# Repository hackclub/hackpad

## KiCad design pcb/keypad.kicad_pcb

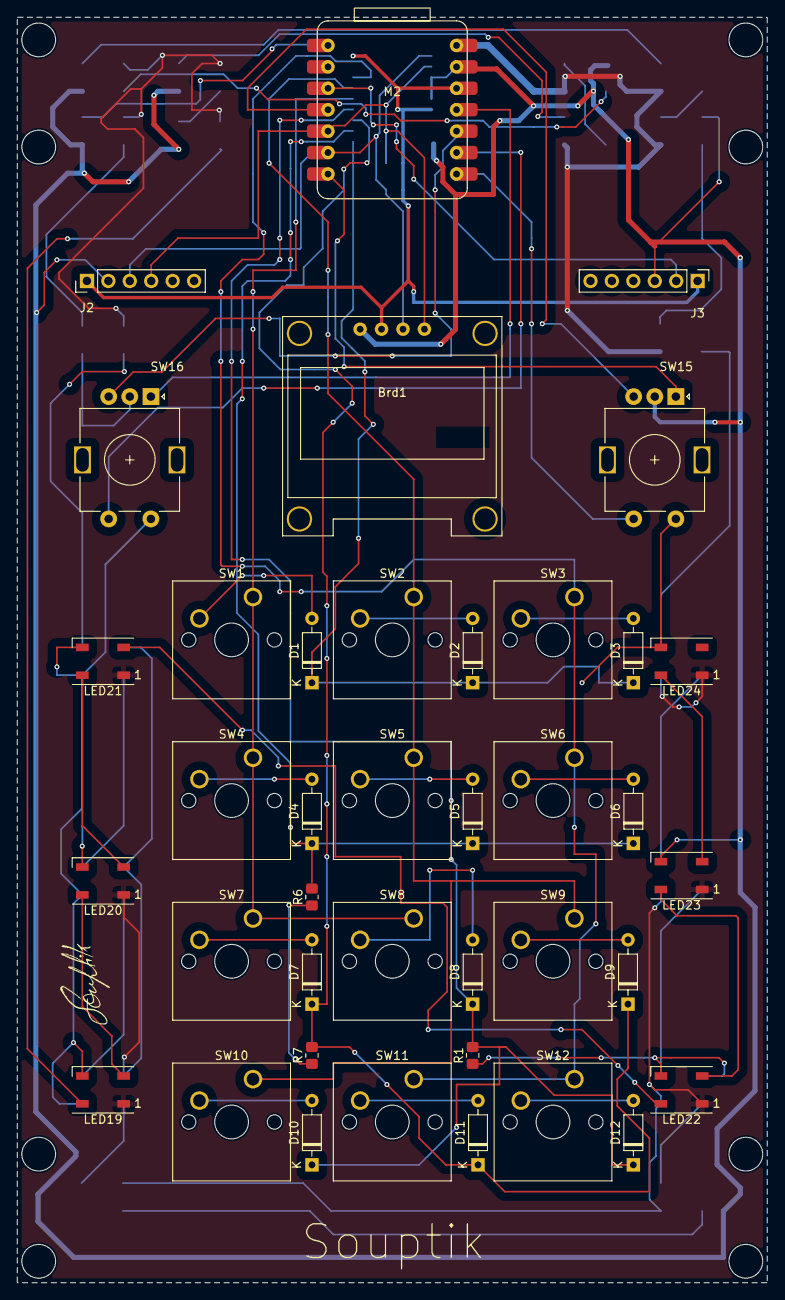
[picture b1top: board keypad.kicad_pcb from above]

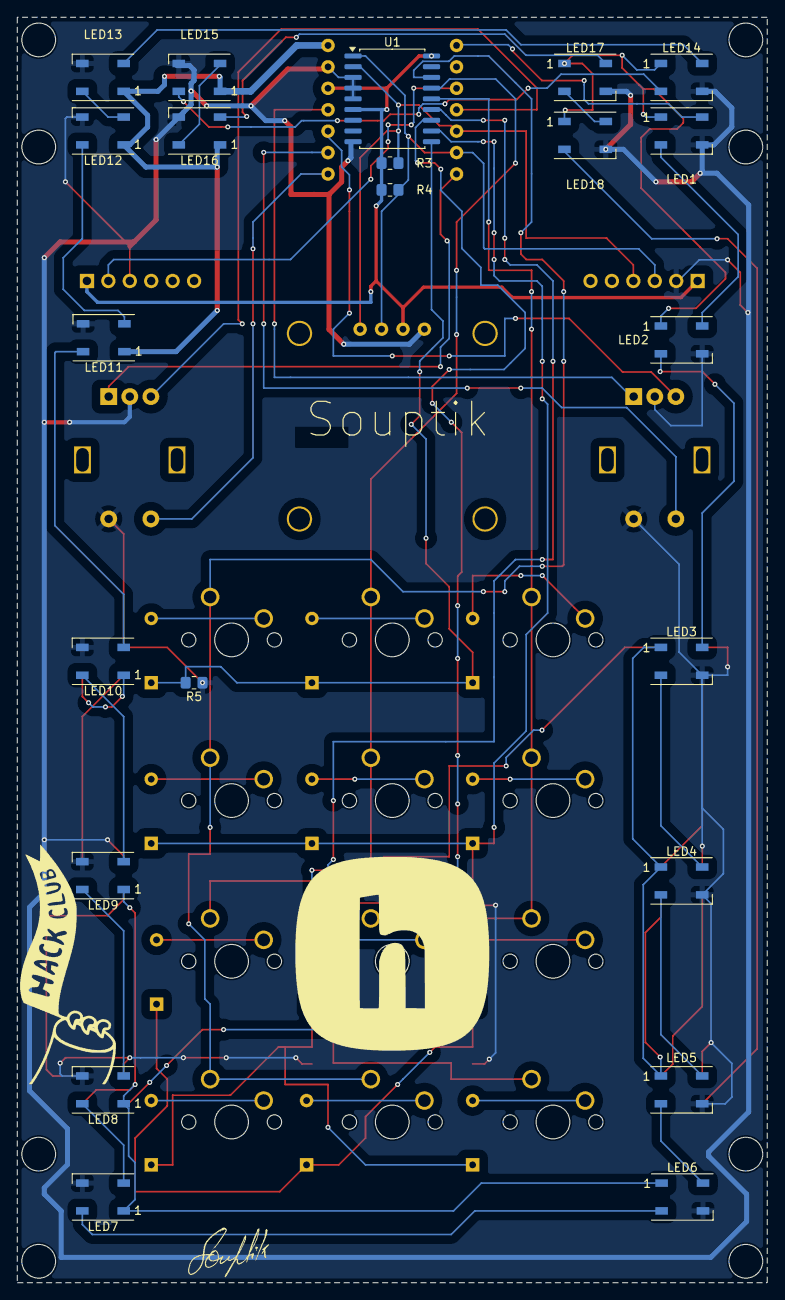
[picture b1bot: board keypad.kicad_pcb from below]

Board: 2 copper layers, 88.9 x 150.0 mm, 61 parts (22 on the bottom side), 55 nets.

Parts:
Brd1: SSD1306; SSD1306_0.96_Oled
D1, D2, D3, D4, D5, D6, D7, D8, D9, D10, D11, D12: D; D_DO-35_SOD27_P7.62mm_Horizontal
J2: VL53L0X; PinHeader_1x06_P2.54mm_Vertical
J3: DHT11; PinHeader_1x06_P2.54mm_Vertical
LED1, LED2, LED3, LED4, LED5, LED6, LED7, LED8, LED9, LED10, LED11, LED12, LED13, LED14, LED15, LED16, LED17, LED18, LED19, LED20, LED21, LED22, LED23, LED24: WS2812B; LED_WS2812B_PLCC4_5.0x5.0mm_P3.2mm
M2: MOUDLE-SEEEDUINO-XIAO; RP2040
R1, R5, R6, R7: 10K; R_0805_2012Metric_Pad1.20x1.40mm_HandSolder
R3, R4: 4.7K; R_0805_2012Metric_Pad1.20x1.40mm_HandSolder
SW1, SW2, SW3, SW4, SW5, SW6, SW7, SW8, SW9, SW10, SW11, SW12: SW_Push_45deg; SW_Cherry_MX_1.00u_PCB
SW15, SW16: RotaryEncoder_Switch; RotaryEncoder_Alps_EC11E-Switch_Vertical_H20mm
U1: MCP23008-xSO; SOIC-18W_7.5x11.6mm_P1.27mm

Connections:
3.3V: Brd1.2 (VCC), J2.1, J3.1, M2.12 (3V3), R3.1, R4.1, U1.6 (~RESET), U1.18 (VDD)
5V: LED1.1 (VDD), LED2.1 (VDD), LED3.1 (VDD), LED4.1 (VDD), LED5.1 (VDD), LED6.1 (VDD), LED7.1 (VDD), LED8.1 (VDD), LED9.1 (VDD), LED10.1 (VDD), LED11.1 (VDD), LED12.1 (VDD), LED13.1 (VDD), LED14.1 (VDD), LED15.1 (VDD), LED16.1 (VDD), LED17.1 (VDD), LED18.1 (VDD), LED19.1 (VDD), LED20.1 (VDD), LED21.1 (VDD), LED22.1 (VDD), LED23.1 (VDD), LED24.1 (VDD), M2.14 (5V)
C0: SW1.1, SW4.1, SW7.1, SW8.1, U1.14 (GP4)
C1: SW2.1, SW5.1, SW9.1, SW10.1, U1.15 (GP5)
C2: SW3.1, SW6.1, SW11.1, SW12.1, U1.16 (GP6)
D2: J3.2, M2.3 (PA10_A2_D2)
DOUT0: LED4.2 (DOUT), LED5.4 (DIN)
DOUT1: LED8.2 (DOUT), LED9.4 (DIN)
DOUT1-1: LED12.2 (DOUT), LED13.4 (DIN)
DOUT2: LED16.2 (DOUT), LED17.4 (DIN)
DOUT2-1: LED20.2 (DOUT), LED21.4 (DIN)
ENC_A: M2.7 (PB08_A6_D6_TX), SW15.A
ENC_A1: M2.11 (PA6_A10_D10_MOSI), SW16.A
ENC_B: M2.4 (PA11_A3_D3), SW15.B
ENC_B1: M2.10 (PA5_A9_D9_MISO), SW16.B
ENC_SW: M2.8 (PB09_A7_D7_RX), SW15.S1
ENC_SW1: M2.9 (PA7_A8_D8_SCK), SW16.S1
GND: Brd1.1 (GND), J2.2, J3.3, LED1.3 (VSS), LED2.3 (VSS), LED3.3 (VSS), LED4.3 (VSS), LED5.3 (VSS), LED6.3 (VSS), LED7.3 (VSS), LED8.3 (VSS), LED9.3 (VSS), LED10.3 (VSS), LED11.3 (VSS), LED12.3 (VSS), LED13.3 (VSS), LED14.3 (VSS), LED15.3 (VSS), LED16.3 (VSS), LED17.3 (VSS), LED18.3 (VSS), LED19.3 (VSS), LED20.3 (VSS), LED21.3 (VSS), LED22.3 (VSS), LED23.3 (VSS), LED24.3 (VSS), M2.13 (GND), R1.1, R5.1, R6.1, R7.1, SW15.C, SW15.S2, SW16.C, SW16.S2, U1.3 (A2), U1.4 (A1), U1.5 (A0), U1.9 (VSS)
unnamed: D1.2 (A), SW1.2
unnamed: D2.2 (A), SW2.2
unnamed: D3.2 (A), SW3.2
unnamed: D4.2 (A), SW4.2
unnamed: D5.2 (A), SW5.2
unnamed: D6.2 (A), SW6.2
unnamed: D7.2 (A), SW7.2
unnamed: D8.2 (A), SW8.2
unnamed: D9.2 (A), SW9.2
unnamed: D10.2 (A), SW10.2
unnamed: D11.2 (A), SW11.2
unnamed: D12.2 (A), SW12.2
unnamed: LED1.2 (DOUT), LED2.4 (DIN)
unnamed: LED2.2 (DOUT), LED3.4 (DIN)
unnamed: LED3.2 (DOUT), LED4.4 (DIN)
unnamed: LED5.2 (DOUT), LED6.4 (DIN)
unnamed: LED6.2 (DOUT), LED7.4 (DIN)
unnamed: LED7.2 (DOUT), LED8.4 (DIN)
unnamed: LED9.2 (DOUT), LED10.4 (DIN)
unnamed: LED10.2 (DOUT), LED11.4 (DIN)
unnamed: LED11.2 (DOUT), LED12.4 (DIN)
unnamed: LED13.2 (DOUT), LED14.4 (DIN)
unnamed: LED14.2 (DOUT), LED15.4 (DIN)
unnamed: LED15.2 (DOUT), LED16.4 (DIN)
unnamed: LED17.2 (DOUT), LED18.4 (DIN)
unnamed: LED18.2 (DOUT), LED19.4 (DIN)
unnamed: LED19.2 (DOUT), LED20.4 (DIN)
unnamed: LED21.2 (DOUT), LED22.4 (DIN)
unnamed: LED22.2 (DOUT), LED23.4 (DIN)
unnamed: LED23.2 (DOUT), LED24.4 (DIN)
R0: D1.1 (K), D2.1 (K), D3.1 (K), R5.2, U1.10 (GP0)
R1: D4.1 (K), D5.1 (K), D6.1 (K), R6.2, U1.11 (GP1)
R2: D7.1 (K), D9.1 (K), D11.1 (K), R7.2, U1.12 (GP2)
R3: D8.1 (K), D10.1 (K), D12.1 (K), R1.2, U1.13 (GP3)
RGB: LED1.4 (DIN), M2.1 (PA02_A0_D0)
SCL: Brd1.3 (SCL), J2.3, M2.6 (PA9_A5_D5_SCL), R4.2, U1.1 (SCL)
SDA: Brd1.4 (SDA), J2.4, M2.5 (PA8_A4_D4_SDA), R3.2, U1.2 (SDA)

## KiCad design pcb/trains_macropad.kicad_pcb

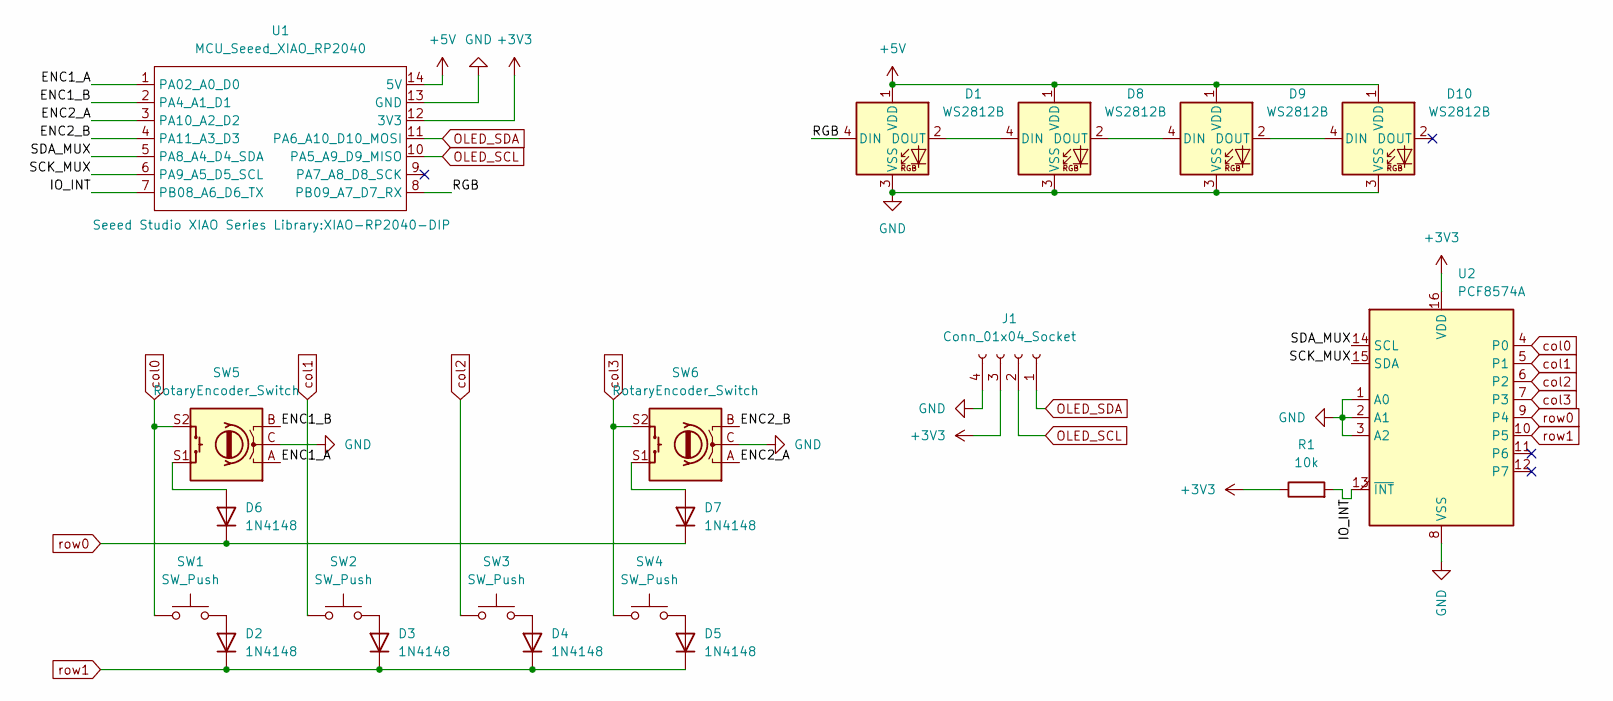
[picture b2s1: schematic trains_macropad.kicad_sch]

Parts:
D1, D8, D9, D10: WS2812B; SK6812-MINI-E
D2, D3, D4, D5, D6, D7: 1N4148; D_DO-35_SOD27_P7.62mm_Horizontal
J1: Conn_01x04_Socket; PinSocket_1x04_P2.54mm_Vertical
R1: 10k; R_Axial_DIN0207_L6.3mm_D2.5mm_P10.16mm_Horizontal
SW1, SW2, SW3, SW4: SW_Push; MXOnly-1U-Hotswap-Antishear
SW5, SW6: RotaryEncoder_Switch; RotaryEncoder_EC11
U1: MCU_Seeed_XIAO_RP2040; XIAO-RP2040-DIP
U2: PCF8574A; DIP-16_W7.62mm

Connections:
+3V3: J1.3, R1.1, U1.12 (3V3), U2.16 (VDD)
+5V: D1.1 (VDD), D8.1 (VDD), D9.1 (VDD), D10.1 (VDD), U1.14 (5V)
/ENC1_A: SW5.A, U1.1 (PA02_A0_D0)
/ENC1_B: SW5.B, U1.2 (PA4_A1_D1)
/ENC2_A: SW6.A, U1.3 (PA10_A2_D2)
/ENC2_B: SW6.B, U1.4 (PA11_A3_D3)
/IO_INT: R1.2, U1.7 (PB08_A6_D6_TX), U2.13 (~INT)
/RGB: D1.4 (DIN), U1.8 (PB09_A7_D7_RX)
/SCK_MUX: U1.6 (PA9_A5_D5_SCL), U2.15 (SDA)
/SDA_MUX: U1.5 (PA8_A4_D4_SDA), U2.14 (SCL)
GND: D1.3 (VSS), D8.3 (VSS), D9.3 (VSS), D10.3 (VSS), J1.4, SW5.C, SW6.C, U1.13 (GND), U2.1 (A0), U2.2 (A1), U2.3 (A2), U2.8 (VSS)
unnamed: D1.2 (DOUT), D8.4 (DIN)
unnamed: D2.2 (A), SW1.2
unnamed: D3.2 (A), SW2.2
unnamed: D4.2 (A), SW3.2
unnamed: D5.2 (A), SW4.2
unnamed: D6.2 (A), SW5.S1
unnamed: D7.2 (A), SW6.S1
unnamed: D8.2 (DOUT), D9.4 (DIN)
unnamed: D9.2 (DOUT), D10.4 (DIN)
OLED_SCL: J1.2, U1.10 (PA5_A9_D9_MISO)
OLED_SDA: J1.1, U1.11 (PA6_A10_D10_MOSI)
col0: SW1.1, SW5.S2, U2.4 (P0)
col1: SW2.1, U2.5 (P1)
col2: SW3.1, U2.6 (P2)
col3: SW4.1, SW6.S2, U2.7 (P3)
row0: D6.1 (K), D7.1 (K), U2.9 (P4)
row1: D2.1 (K), D3.1 (K), D4.1 (K), D5.1 (K), U2.10 (P5)

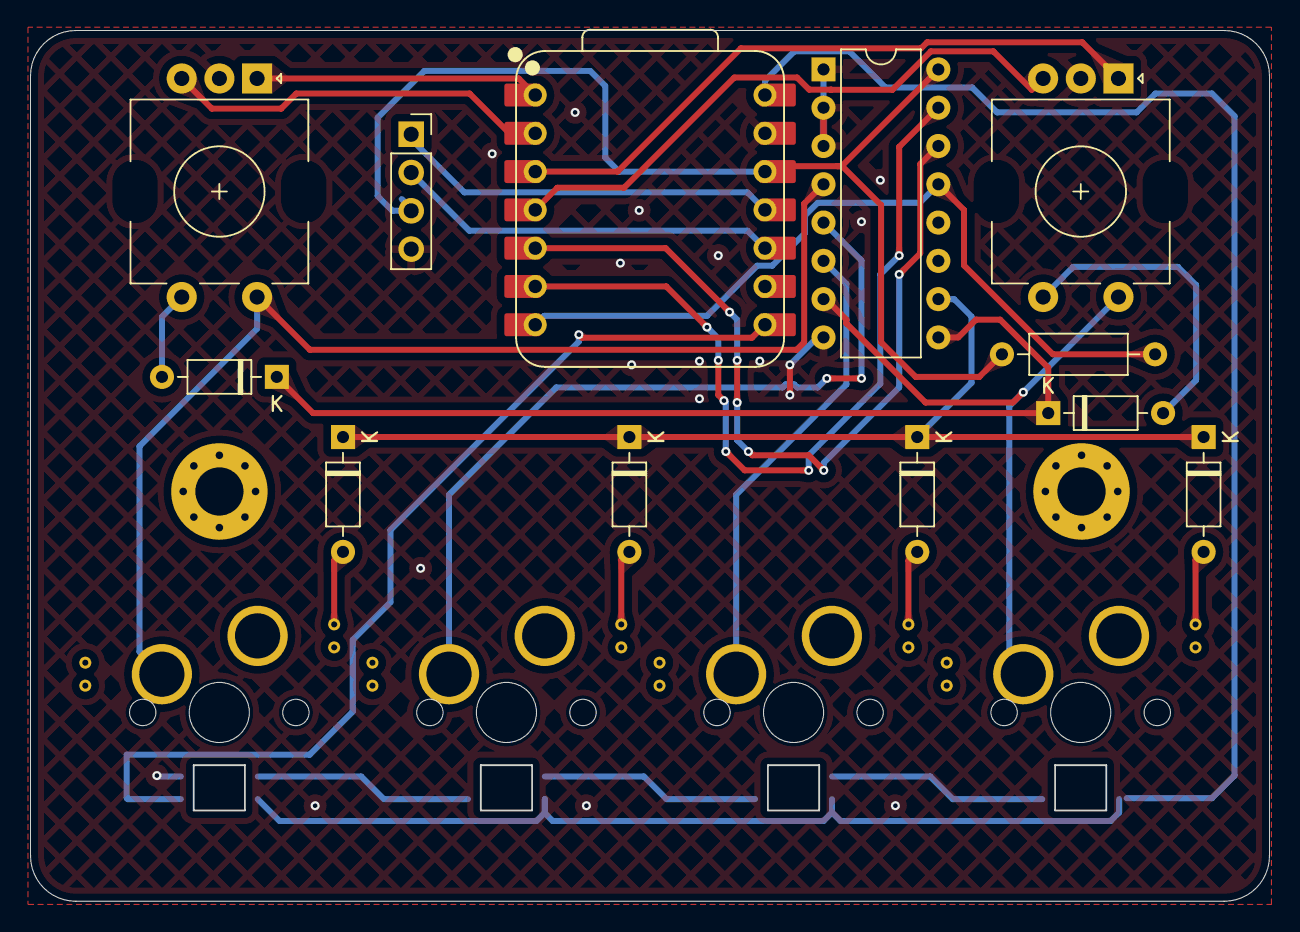
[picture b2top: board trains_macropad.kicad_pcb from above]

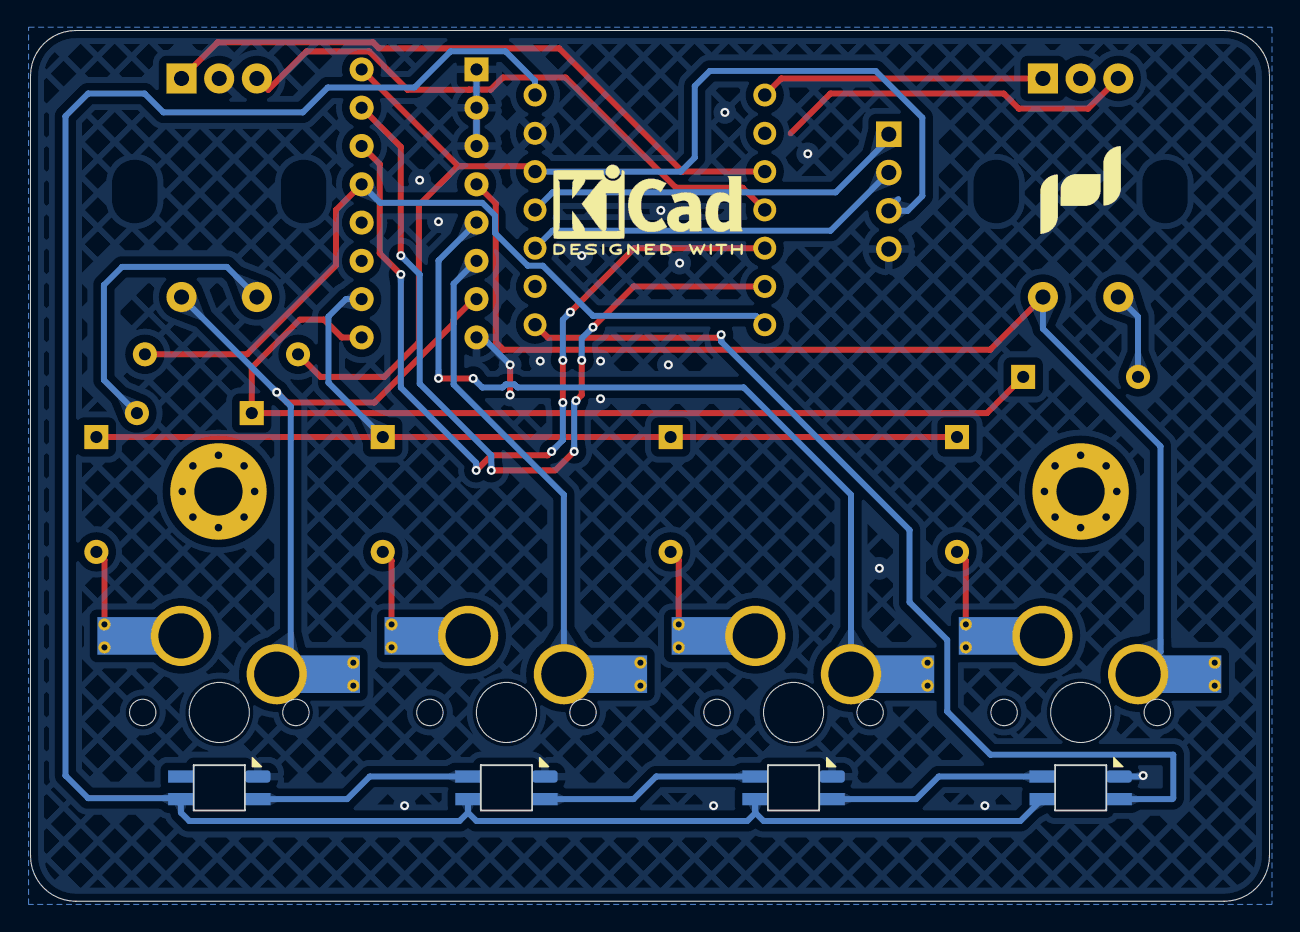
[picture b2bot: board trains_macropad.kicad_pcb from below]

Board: 2 copper layers, 82.2 x 57.8 mm, 20 parts (4 on the bottom side), 28 nets.

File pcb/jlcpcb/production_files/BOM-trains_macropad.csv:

Comment,Designator,Footprint,LCSC
RotaryEncoder_Switch,SW6,RotaryEncoder_EC11,
RotaryEncoder_Switch,SW5,RotaryEncoder_EC11,
WS2812B,D10,SK6812-MINI-E,
WS2812B,D9,SK6812-MINI-E,
WS2812B,D8,SK6812-MINI-E,
WS2812B,D1,SK6812-MINI-E,
1N4148,D7,D_DO-35_SOD27_P7.62mm_Horizontal,
MCU_Seeed_XIAO_RP2040,U1,XIAO-RP2040-DIP,
SW_Push,SW4,MXOnly-1U-Hotswap-Antishear,
PCF8574A,U2,DIP-16_W7.62mm,
10k,R1,R_Axial_DIN0207_L6.3mm_D2.5mm_P10.16mm_Horizontal,
1N4148,D5,D_DO-35_SOD27_P7.62mm_Horizontal,
1N4148,D6,D_DO-35_SOD27_P7.62mm_Horizontal,
1N4148,D3,D_DO-35_SOD27_P7.62mm_Horizontal,
SW_Push,SW2,MXOnly-1U-Hotswap-Antishear,
SW_Push,SW1,MXOnly-1U-Hotswap-Antishear,
1N4148,D4,D_DO-35_SOD27_P7.62mm_Horizontal,
Conn_01x04_Socket,J1,PinSocket_1x04_P2.54mm_Vertical,
SW_Push,SW3,MXOnly-1U-Hotswap-Antishear,
1N4148,D2,D_DO-35_SOD27_P7.62mm_Horizontal,

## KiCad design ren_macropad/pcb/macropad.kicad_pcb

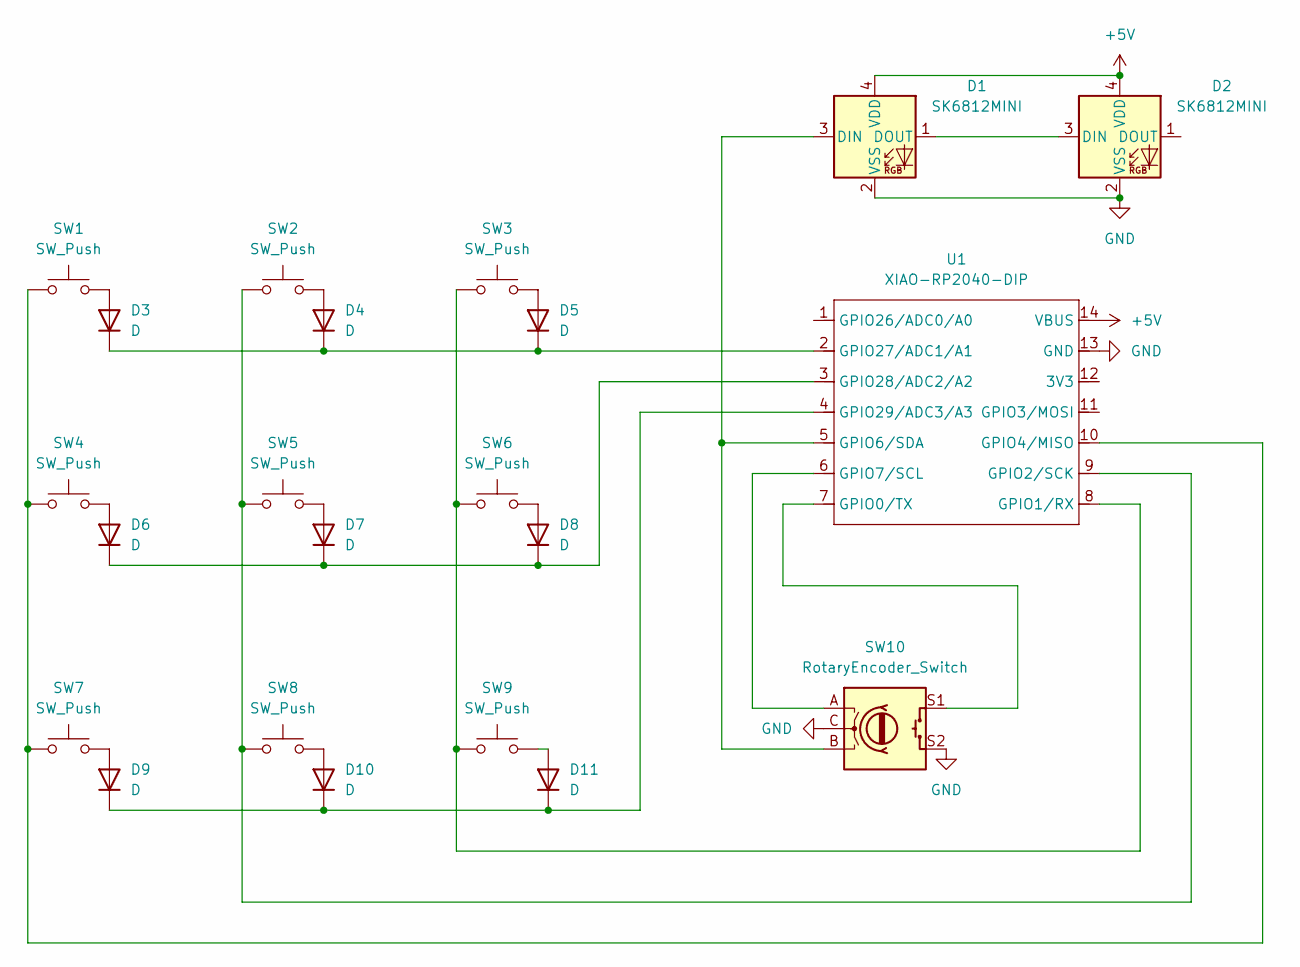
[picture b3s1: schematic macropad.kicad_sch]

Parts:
D1, D2: SK6812MINI; LED_SK6812MINI_PLCC4_3.5x3.5mm_P1.75mm
D3, D4, D5, D6, D7, D8, D9, D10, D11: D; D_DO-35_SOD27_P7.62mm_Horizontal
SW1, SW2, SW3, SW4, SW5, SW6, SW7, SW8, SW9: SW_Push; SW_Cherry_MX_1.00u_PCB
SW10: RotaryEncoder_Switch; RotaryEncoder_Alps_EC11E-Switch_Vertical_H20mm_CircularMoun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
U1: XIAO-RP2040-DIP

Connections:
+5V: D1.4 (VDD), D2.4 (VDD), U1.14 (VBUS)
GND: D1.2 (VSS), D2.2 (VSS), SW10.C, SW10.S2, U1.13 (GND)
unnamed: D1.3 (DIN), SW10.B, U1.5 (GPIO6/SDA)
unnamed: D1.1 (DOUT), D2.3 (DIN)
unnamed: D3.2 (A), SW1.2
unnamed: D3.1 (K), D4.1 (K), D5.1 (K), U1.2 (GPIO27/ADC1/A1)
unnamed: D4.2 (A), SW2.2
unnamed: D5.2 (A), SW3.2
unnamed: D6.2 (A), SW4.2
unnamed: D6.1 (K), D7.1 (K), D8.1 (K), U1.3 (GPIO28/ADC2/A2)
unnamed: D7.2 (A), SW5.2
unnamed: D8.2 (A), SW6.2
unnamed: D9.2 (A), SW7.2
unnamed: D10.2 (A), SW8.2
unnamed: D9.1 (K), D10.1 (K), D11.1 (K), U1.4 (GPIO29/ADC3/A3)
unnamed: D11.2 (A), SW9.2
unnamed: SW10.S1, U1.7 (GPIO0/TX)
unnamed: SW3.1, SW6.1, SW9.1, U1.8 (GPIO1/RX)
unnamed: SW2.1, SW5.1, SW8.1, U1.9 (GPIO2/SCK)
unnamed: SW1.1, SW4.1, SW7.1, U1.10 (GPIO4/MISO)
unnamed: SW10.A, U1.6 (GPIO7/SCL)

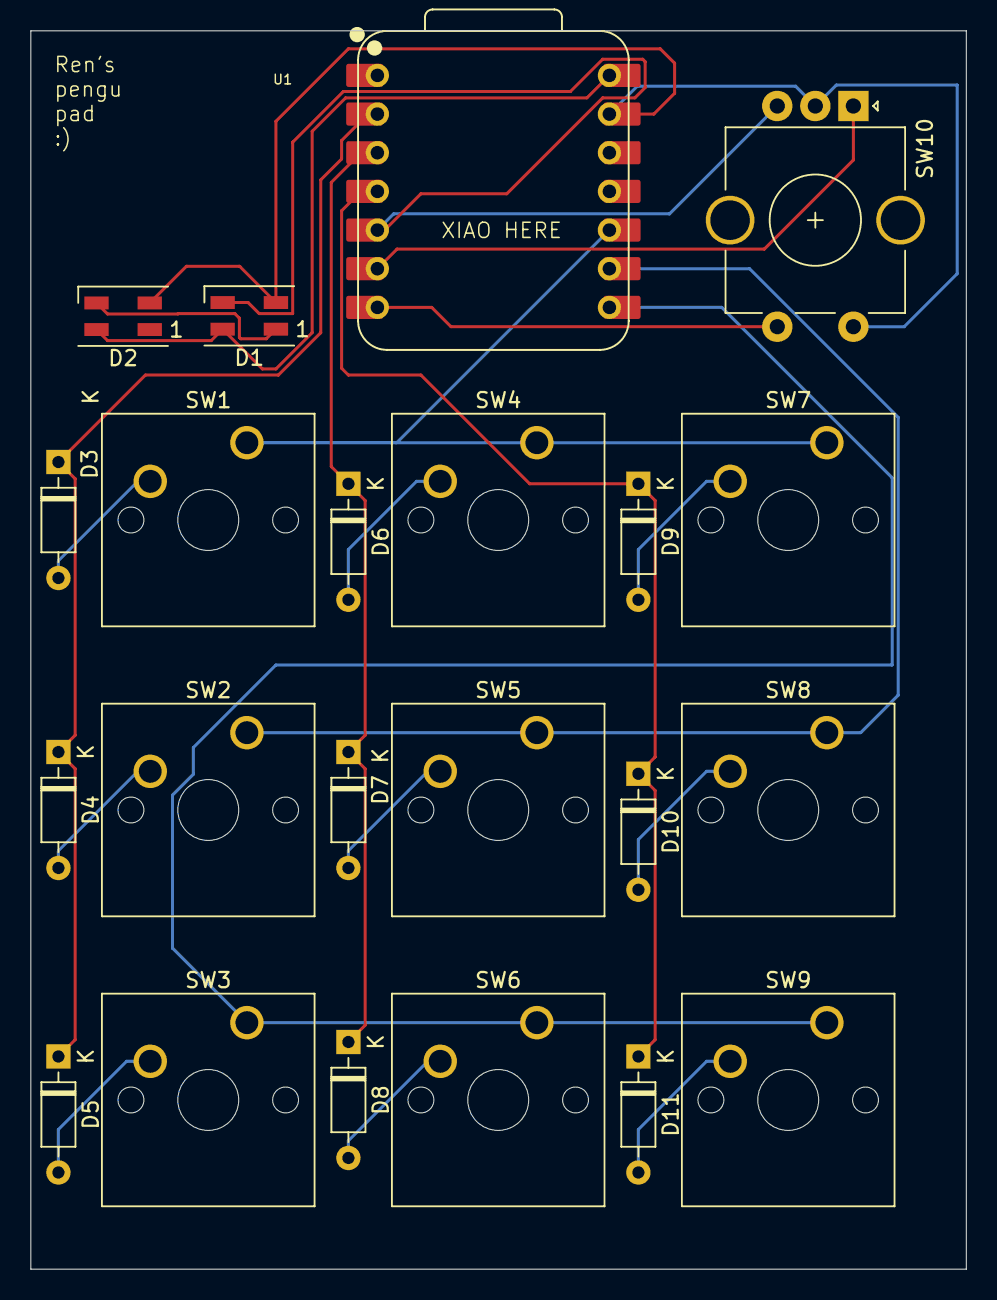
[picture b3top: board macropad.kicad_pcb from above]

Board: 2 copper layers, 61.5 x 81.4 mm, 22 parts (0 on the bottom side), 21 nets.
